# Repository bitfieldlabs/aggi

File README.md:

AFTERGLOW GI is a WPC pinball machine extension board that aims at softening the hard light on/off transitions that result in replacing the original GI incandescent bulbs with LEDs.

The brain of the board is a Arduino nano. It monitors the triac signals on the WPC bus and adjusts the PWM of the GI lines accordingly in order to dim the LEDs. For this purpose the whole GI is powered on DC voltage as opposed to the original AC 6.3V.

There are two options to power the Afterglow GI board and all GI LEDs:

:open_file_folder: [afterglow_gi_nano](https://github.com/bitfieldlabs/aggi/tree/master/afterglow_gi_nano)<br>
Board revision 1.0 needs to be powered from an external power supply. Recommended is a 12V supply delivering at least 8A.

:open_file_folder: [afterglow_gi_nano_ps](https://github.com/bitfieldlabs/aggi/tree/master/afterglow_gi_nano_ps)<br>
Board revision 1.1 features a power supply and can be attached to the WPC power supply's 6.3V AC connector directly.

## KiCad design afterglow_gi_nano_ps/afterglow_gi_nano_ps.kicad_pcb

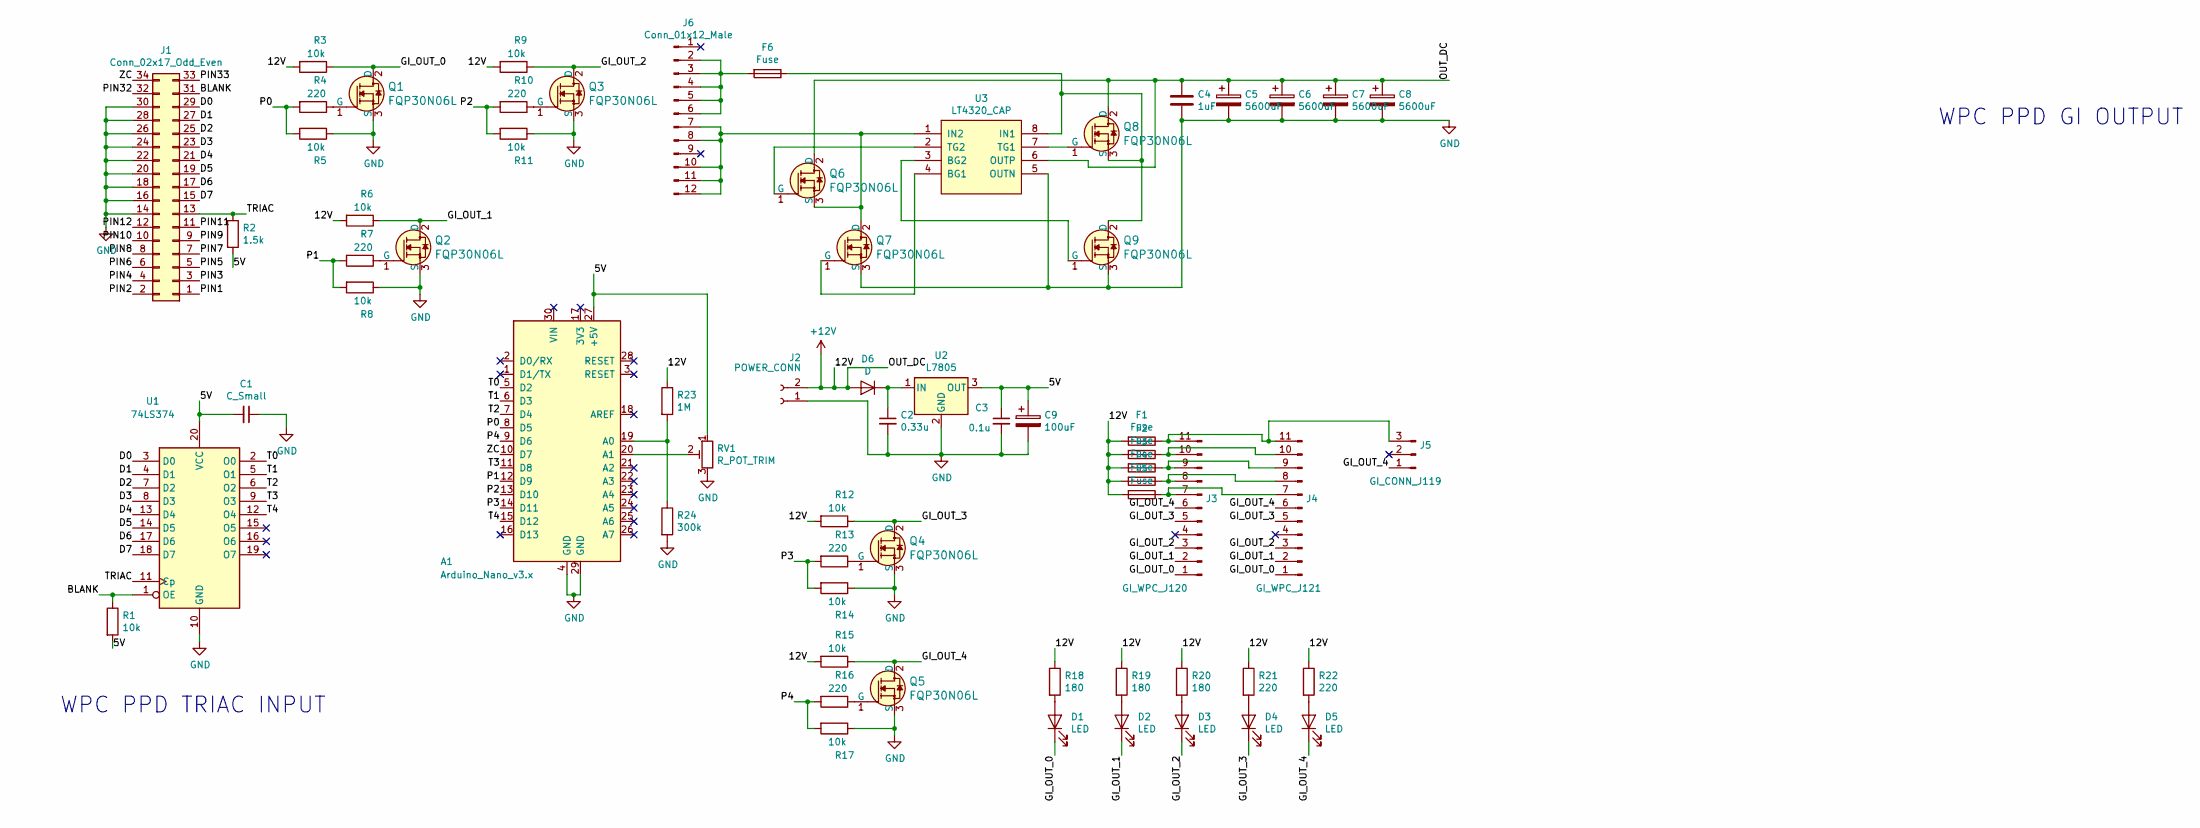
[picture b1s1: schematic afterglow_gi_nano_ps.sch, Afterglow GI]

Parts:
A1: Arduino_Nano_v3.x; Arduino_Nano
C1: C_Small; C_0805_HandSoldering
C2: 0.33u; C_0805_HandSoldering
C3: 0.1u; C_0805_HandSoldering
C4: 1uF; C_Rect_L7.0mm_W3.5mm_P5.00mm
C5, C6, C7, C8: 5600uF; CP_Radial_D18.0mm_P7.50mm
C9: 100uF; CP_Radial_D8.0mm_P3.50mm
D1, D2, D3, D4, D5: LED; LED_0805_HandSoldering
D6: D; D_5W_P10.16mm_Horizontal
F1, F2, F3, F4, F5, F6: Fuse; Fuseholder5x20_horiz_open_lateral_Type-II
J1: Conn_02x17_Odd_Even; IDC_Header_Straight_34pins
J2: POWER_CONN; TerminalBlock_Philmore_TB132_02x5mm_Straight
J3: GI_WPC_J120; Molex_KK-41791-11_10x3.96mm_Straight
J4: GI_WPC_J121; Molex_KK-41791-11_10x3.96mm_Straight
J5: GI_CONN_J119; Molex_KK-41791-03_03x3.96mm_Straight
J6: Conn_01x12_Male; Molex_KK-41791-12_10x3.96mm_Straight
Q1, Q2, Q3, Q4, Q5, Q6, Q7, Q8, Q9: FQP30N06L; TO-220_Vertical; MPN FQP30N06L; Digi-Key_PN FQP30N06L-ND
R1, R3, R5, R6, R8, R9, R11, R12, R14, R15, R17: 10k; R_0805_HandSoldering
R2: 1.5k; R_0805_HandSoldering
R4, R7, R10, R13, R16, R21, R22: 220; R_0805_HandSoldering
R18, R19, R20: 180; R_0805_HandSoldering
R23: 1M; R_0805_HandSoldering
R24: 300k; R_0805_HandSoldering
RV1: R_POT_TRIM; Potentiometer_Trimmer_Piher_PT-10v10_Horizontal_Px10.0mm_Py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
U1: 74LS374; SOIC-20W_7.5x12.8mm_Pitch1.27mm
U2: L7805; TO-220_Vertical
U3: LT4320_CAP; DIP-8_W7.62mm_LongPads

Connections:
+12V: C4.1, C5.1, C6.1, C7.1, C8.1, D6.2 (A), F1.2, F2.2, F3.2, F4.2, F5.2, J2.2, Q6.2 (D), Q8.2 (D), R3.2, R6.2, R9.2, R12.2, R15.2, R18.1, R19.1, R20.1, R21.1, R22.1, R23.1, U3.6 (OUTP)
/5V: A1.27 (+5V), C1.2, C3.1, C9.1, R1.2, R2.2, RV1.1, U1.20 (VCC), U2.3 (OUT)
/BLANK: J1.31, R1.1, U1.1 (OE)
/D0: J1.29, U1.3 (D0)
/D1: J1.27, U1.4 (D1)
/D2: J1.25, U1.7 (D2)
/D3: J1.23, U1.8 (D3)
/D4: J1.21, U1.13 (D4)
/D5: J1.19, U1.14 (D5)
/D6: J1.17, U1.17 (D6)
/D7: J1.15, U1.18 (D7)
/GI_OUT_0: D1.1 (K), J3.1, J4.1, Q1.2 (D), R3.1
/GI_OUT_1: D2.1 (K), J3.2, J4.2, Q2.2 (D), R6.1
/GI_OUT_2: D3.1 (K), J3.3, J4.3, Q3.2 (D), R9.1
/GI_OUT_3: D4.1 (K), J3.5, J4.5, Q4.2 (D), R12.1
/GI_OUT_4: D5.1 (K), J3.6, J4.6, J5.1, Q5.2 (D), R15.1
/P0: A1.8 (D5), R4.2, R5.2
/P1: A1.12 (D9), R7.2, R8.2
/P2: A1.13 (D10), R10.2, R11.2
/P3: A1.14 (D11), R13.2, R14.2
/P4: A1.9 (D6), R16.2, R17.2
/PIN1: J1.1
/PIN2: J1.2
/PIN3: J1.3
/PIN4: J1.4
/PIN5: J1.5
/PIN6: J1.6
/PIN7: J1.7
/PIN8: J1.8
/PIN9: J1.9
/PIN10: J1.10
/PIN11: J1.11
/PIN12: J1.12
/PIN32: J1.32
/PIN33: J1.33
/T0: A1.5 (D2), U1.2 (O0)
/T1: A1.6 (D3), U1.5 (O1)
/T2: A1.7 (D4), U1.6 (O2)
/T3: A1.11 (D8), U1.9 (O3)
/T4: A1.15 (D12), U1.12 (O4)
/TRIAC: J1.13, R2.1, U1.11 (Cp)
/ZC: A1.10 (D7), J1.34
GND: A1.4 (GND), A1.29 (GND), C1.1, C2.2, C3.2, C4.2, C5.2, C6.2, C7.2, C8.2, C9.2, J1.14, J1.16, J1.18, J1.20, J1.22, J1.24, J1.26, J1.28, J1.30, J2.1, Q1.3 (S), Q2.3 (S), Q3.3 (S), Q4.3 (S), Q5.3 (S), Q7.3 (S), Q9.3 (S), R5.1, R8.1, R11.1, R14.1, R17.1, R24.2, RV1.3, U1.10 (GND), U2.2 (GND), U3.5 (OUTN)
unnamed: A1.19 (A0), R23.2, R24.1
unnamed: A1.20 (A1), RV1.2
unnamed: C2.1, D6.1 (K), U2.1 (IN)
unnamed: D1.2 (A), R18.2
unnamed: D2.2 (A), R19.2
unnamed: D3.2 (A), R20.2
unnamed: D4.2 (A), R21.2
unnamed: D5.2 (A), R22.2
unnamed: F1.1, J3.11, J4.11, J5.3
unnamed: F2.1, J3.10, J4.10
unnamed: F3.1, J3.9, J4.9
unnamed: F4.1, J3.8, J4.8
unnamed: F5.1, J3.7, J4.7
unnamed: F6.1, Q8.3 (S), Q9.2 (D), U3.8 (IN1)
unnamed: F6.2, J6.2, J6.3, J6.4, J6.5, J6.6
unnamed: J6.7, J6.8, J6.10, J6.11, J6.12, Q6.3 (S), Q7.2 (D), U3.1 (IN2)
unnamed: Q1.1 (G), R4.1
unnamed: Q2.1 (G), R7.1
unnamed: Q3.1 (G), R10.1
unnamed: Q4.1 (G), R13.1
unnamed: Q5.1 (G), R16.1
unnamed: Q6.1 (G), U3.2 (TG2)
unnamed: Q7.1 (G), U3.4 (BG1)
unnamed: Q8.1 (G), U3.7 (TG1)
unnamed: Q9.1 (G), U3.3 (BG2)

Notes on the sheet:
WPC PPD TRIAC INPUT
WPC PPD GI OUTPUT

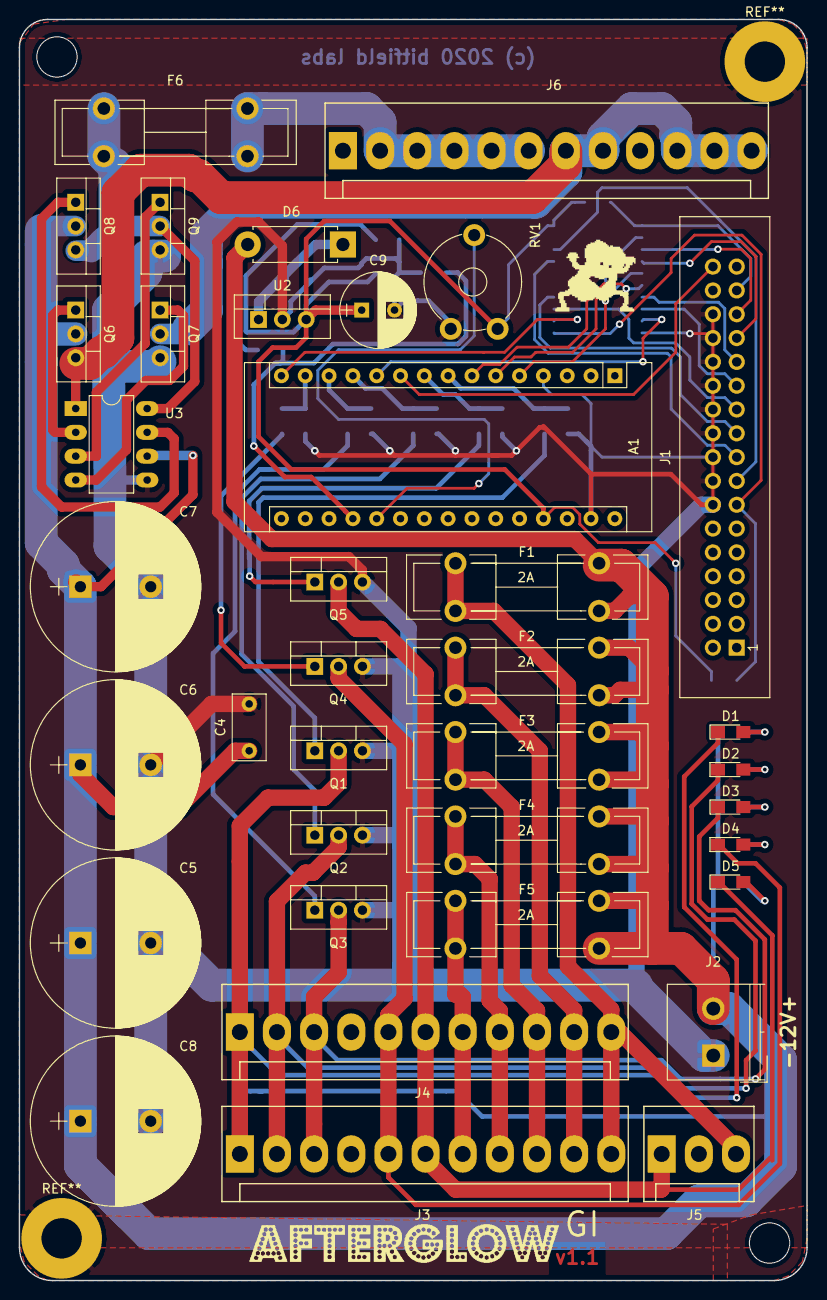
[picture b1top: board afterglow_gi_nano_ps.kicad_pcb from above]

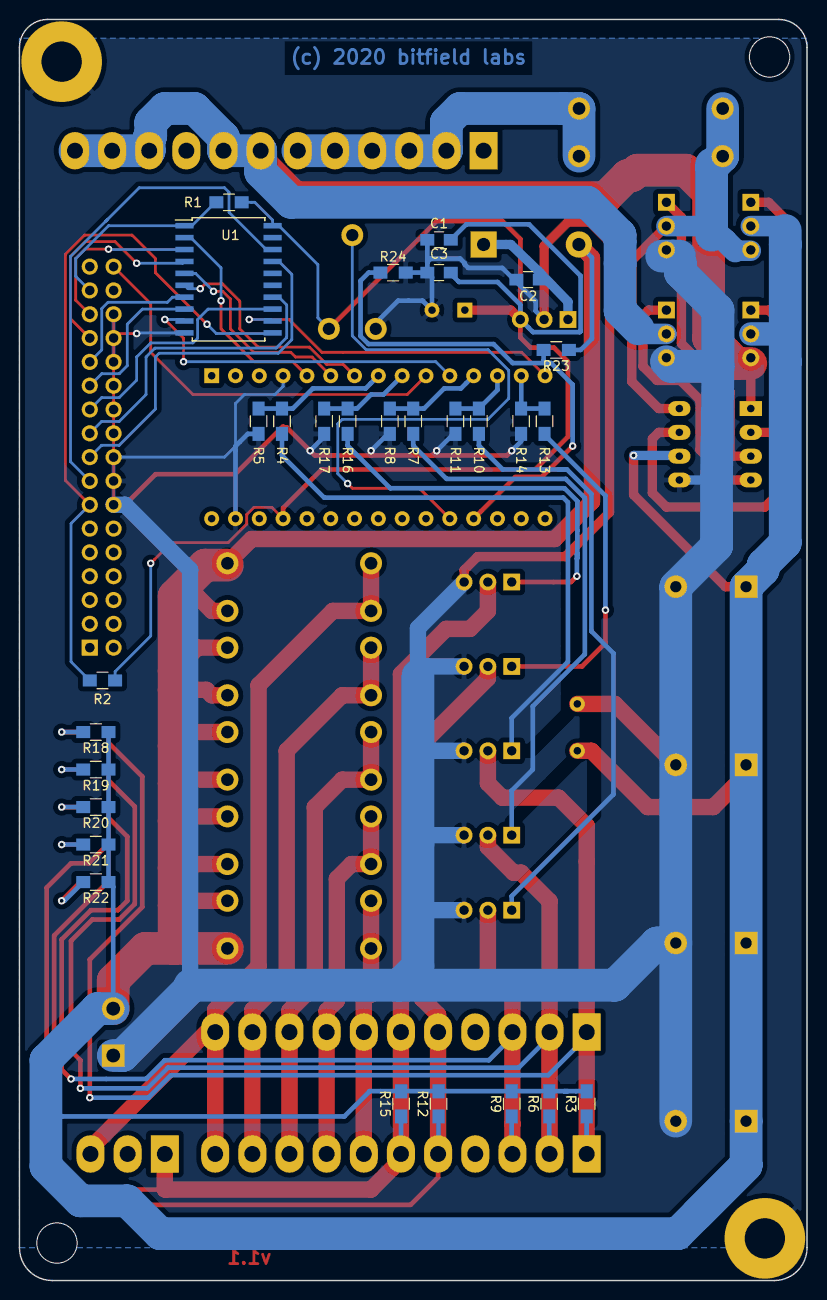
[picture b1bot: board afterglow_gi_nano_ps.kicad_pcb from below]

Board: 2 copper layers, 84.0 x 134.5 mm, 67 parts (28 on the bottom side), 54 nets.

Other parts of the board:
FLAKIE: FLAKIE_inv
afterglow: afterglow

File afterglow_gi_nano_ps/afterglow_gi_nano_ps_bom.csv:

"Id";"Designator";"Package";"Quantity";"Designation";"Supplier and ref";
1;"C9";"CP_Radial_D8.0mm_P3.50mm";1;"100uF";;;
2;"REF**,REF**";"MountingHole_4.3mm_M4_Pad";2;"MountingHole_4.3mm_M4_Pad";;;
3;"C4";"C_Rect_L7.0mm_W3.5mm_P5.00mm";1;"1uF";;;
4;"U3";"DIP-8_W7.62mm_LongPads";1;"LT4320_CAP";;;
5;"Q9,Q8,Q7,Q6,Q1,Q2,Q3,Q4,Q5";"TO-220_Vertical";9;"FQP30N06L";;;
6;"J6";"Molex_KK-41791-12_10x3.96mm_Straight";1;"Conn_01x12_Male";;;
7;"F6,F1,F2,F3,F4,F5";"Fuseholder5x20_horiz_open_lateral_Type-II";6;"Fuse";;;
8;"C8,C7,C6,C5";"CP_Radial_D18.0mm_P7.50mm";4;"5600uF";;;
9;",";"MountingHole_4.3mm_M4_DIN965";2;"MountingHole_4.3mm_M4_DIN965";;;
10;"RV1";"Potentiometer_Trimmer_Piher_PT-10v10_Horizontal_Px10.0mm_Py5.0mm";1;"R_POT_TRIM";;;
11;"J2";"TerminalBlock_Philmore_TB132_02x5mm_Straight";1;"POWER_CONN";;;
12;"U1";"SOIC-20W_7.5x12.8mm_Pitch1.27mm";1;"74LS374";;;
13;"A1";"Arduino_Nano";1;"Arduino_Nano_v3.x";;;
14;"C1";"C_0805_HandSoldering";1;"C_Small";;;
15;"C2";"C_0805_HandSoldering";1;"0.33u";;;
16;"C3";"C_0805_HandSoldering";1;"0.1u";;;
17;"D1,D2,D3,D4,D5";"LED_0805_HandSoldering";5;"LED";;;
18;"D6";"D_5W_P10.16mm_Horizontal";1;"D";;;
19;"J1";"IDC_Header_Straight_34pins";1;"Conn_02x17_Odd_Even";;;
20;"J3";"Molex_KK-41791-11_10x3.96mm_Straight";1;"GI_WPC_J120";;;
21;"J4";"Molex_KK-41791-11_10x3.96mm_Straight";1;"GI_WPC_J121";;;
22;"J5";"Molex_KK-41791-03_03x3.96mm_Straight";1;"GI_CONN_J119";;;
23;"R1,R3,R5,R6,R8,R9,R11,R12,R14,R15,R17";"R_0805_HandSoldering";11;"10k";;;
24;"R2";"R_0805_HandSoldering";1;"1.5k";;;
25;"R4,R7,R10,R13,R16,R21,R22";"R_0805_HandSoldering";7;"220";;;
26;"R18,R19,R20";"R_0805_HandSoldering";3;"180";;;
27;"R23";"R_0805_HandSoldering";1;"1M";;;
28;"R24";"R_0805_HandSoldering";1;"300k";;;
29;"U2";"TO-220_Vertical";1;"L7805";;;
30;"FLAKIE";"FLAKIE_inv";1;"";;;
31;"afterglow";"afterglow";1;"";;;

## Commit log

2018-12-31 Let's get started!
2019-01-01 tut was
2019-01-01 weiter geht's
2019-01-02 Some docu
2019-01-04 More progress
2019-01-04 Use the Arduino PWM pins
2019-01-04 docu
2019-01-04 PWM seems to work now
2019-01-05 Fixed an interrupt issue
2019-01-05 Robustness
2019-01-05 The upside down
2019-01-05 Better brightness handling
2019-01-05 Started with the schematic
2019-01-06 Fixed brightness level 6
2019-01-06 Schematic progress
2019-01-06 Schematic progressing
2019-02-18 Designing the PCB
2019-02-19 Some PCB progress
2019-02-24 First PCB draft complete
2019-02-24 PCB v1.00 ready
2019-02-24 PCB cosmetics
2019-05-04 Cleanup
2019-05-11 Smooth transitions
2019-05-12 Stable division
2019-05-12 One histogram per string
2019-05-25 Added schematic pdf and BOM
2019-05-26 some images
2019-05-26 Support for the global brightness poti
2019-12-27 Use a logarithmic brightness distribution
2020-01-08 Added footprint position files
2020-01-29 Added PS draft
2020-02-09 A PCB layout proposal
2020-02-09 New PCB layout with power supply
2020-02-09 Some progress
2020-02-09 Added power supply schematic
2020-02-09 New power supply
2020-02-14 PCB cosmetix
2020-02-21 Added position files and BOM
2020-02-28 Added missing C4 footprint, grounding pads
2020-02-28 Added 5V stabilizing capacitor
2020-03-03 Added PS BOM and schematic
2020-05-02 Fixed a routing error around C4
2020-06-02 Some labelling
2020-06-05 Added AFTERGLOW GI logo
2020-06-05 Upaded PCB v1.1 Gerber files
2020-06-05 Added a PCB v1.1 rendering
2020-11-19 Centroid file
2020-11-20 Measure the input voltage

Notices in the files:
afterglow_gi_nano_ps/afterglow_gi_nano_ps.kicad_pcb:
(c) 2020 bitfield labs
